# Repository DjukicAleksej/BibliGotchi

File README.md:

<div align="center">

# 🎮 BibliGotchi

<p align="center" style="font-size: 1.1em; max-width: 800px; line-height: 1.6;">
  A custom-made Tamagotchi with a heavenly touch. Made by a 17-year-old from Bosnia and Herzegovina, this project showcases my learning journey in the hardware ecosystem. I designed this using KiCad for the PCB, OnShape for the structural case, and the Arduino IDE for the firmware.
</p>

<p align="center" style="max-width: 800px; line-height: 1.6;">
  This Tamagotchi features 3 main tracking stats: <strong>Hunger</strong>, <strong>Energy</strong>, and <strong>Happiness</strong>. You can improve these parameters by physically interacting with the device using tactile buttons—each mapped to mapped behaviors like playing, feeding, or sleeping. Depending on active stats, 4 distinct screen expressions dynamically cycle: neutral, happy, sad, or sleeping. All 32x32 pixel sprites are custom-drawn, giving you the template to easily drop in your own custom artwork!
</p>

## 💡 Why Did I Build This?

<p align="center" style="max-width: 800px; line-height: 1.6;">
  I built this project to qualify for <strong>Fallout</strong>, a hardware hackathon organized by the non-profit community <strong>Hack Club</strong>. I gravitated toward building a Tamagotchi because it sits at the perfect crossroads: complex enough to challenge my design skills, yet interactive enough to stand out. In a world saturated with purely web-based apps, having a tangible, physical device makes it uniquely engaging. Through this process, I significantly deepened my understanding of firmware architecture and structural enclosure engineering.
</p>

---

<p align="center">
  <a href="Zine.pdf">📖 Read the Zine</a>
  &nbsp;&nbsp;•&nbsp;&nbsp;
  <a href="PCB-Files/Gerbers.zip">📦 Download Gerbers</a>
  &nbsp;&nbsp;•&nbsp;&nbsp;
  <a href="Case-Files/">📐 STEP Case Files</a>
  &nbsp;&nbsp;•&nbsp;&nbsp;
  <a href="BOM/BOM.csv">🧾 PCB BOM</a>
</p>

---

</div>

## 🔍 Overview
BibliGotchi is built around the **Seeed Studio XIAO ESP32-C3**, utilizing a custom PCB routed in KiCad to interface all peripherals smoothly. 

### Key Features:
* **Display**: 0.96" OLED screen for crisp UI rendering.
* **Power**: Integrated 3.7V 500mAh lithium-polymer battery.
* **Audio & Input**: Passive buzzer for alerts alongside 3 interactive navigation switches.
* **Enclosure**: Modeled inside OnShape ([View OnShape CAD Here](https://cad.onshape.com/documents/44d918d4bf107306610f1545/w/f7f086a823beff1369bb4e84/e/70df229ea8fe1c8cd39e3565)). Features filleted edge-geometry to completely eliminate sharp surfaces, precise cutouts for the USB-C port, and an internal structural sub-enclosure. The battery is safely clamped using a dual-screw retention bracket.
* **Firmware**: Written in C++ targeting the Arduino runtime environment. It implements real-time lifecycle status loops (tracking age, happiness levels, and depletion intervals) rendered via custom graphical progress bars.

---

## 📐 Case Gallery

| Top View | Top Side View |
| :---: | :---: |
|  |  |
| **Bottom View** | **Exploded View** |
|  |  |

---

## ⚡ PCB Gallery

| Top View 1 | Top View 2 |
| :---: | :---: |
|  |  |
| **Bottom View 1** | **Bottom View 2** |
|  |  |

### Schematic

---

## 🗺️ Trace Routing

| Top Routing Layer | Bottom Routing Layer |
| :---: | :---: |
|  |  |

---

### 🛠️ Bill of Materials (BOM)

| Item | Description | Value | LCSC Part | Qty | MOQ | Unit Price | Total Price | Resources |
| :--- | :--- | :--- | :--- | :---: | :---: | :---: | :---: | :--- |
| Battery | Single-cell battery | Battery_Cell | | 1 | 1 | $5.11 | $5.11 | [Datasheet](https://www.kiwi-electronics.com/image/catalog/pdf/LP503035%20500mAh%203.7V%20%28AD306053%29%2020230615%5B34%5D.pdf), [Purchase Link](https://www.aliexpress.com/item/1005006043243361.html) |
| Buzzer | Passive Buzzer | 1207-P6.5MM | C49246964 | 1 | 10 | $0.03 | $0.32 | [Datasheet](https://www.lcsc.com/datasheet/C49246964.pdf), [Purchase Link](https://www.lcsc.com/product-detail/C49246964.html) |
| Switch | Push button switch, generic, two pins | SW_Push | C2888493 | 3 | 50 | $0.01 | $0.54 | [Datasheet](https://www.lcsc.com/datasheet/C2888493.pdf), [Purchase Link](https://www.lcsc.com/product-detail/C2888493.html) |
| ESP32-C3 MCU | IoT mini development board | XIAO-ESP32-C3-SMD | | 1 | 1 | $5.67 | $5.67 | [Datasheet](https://files.seeedstudio.com/wiki/XIAO_WiFi/Resources/esp32-c3_datasheet.pdf), [Purchase Link](https://www.aliexpress.com/item/1005006979844970.html) |
| OLED Display | 0.96" Inch OLED Display | HS96L03W2C03 | C5248080 | 1 | 1 | $2.24 | $2.24 | [Datasheet](https://www.lcsc.com/datasheet/C5248080.pdf), [Purchase Link](https://www.lcsc.com/product-detail/C5248080.html) |
| PCB | Hardware Fabrication Support | - | - | 1 | 5 | - | $4.00 | - |
| PCB Shipping | Shipping for the PCB, its kinda expensive cause I live outside the EU | - | - | - | - | - | $26.00 | - |
| **Total** | | | | **8** | **68** | **$13.10** | **$43.88** | |

### ⚙️ Structural Fasteners (Build BOM)

| Item | Description | Quantity | Total Price |
| :--- | :--- | :---: | :--- |
| M3 L20 Screws | Connects the structural Bottom and Top case layers while mounting the internal PCB safely | 2 | $0.10 
| M2 Screws L8mm | Shorter structural screws allocated to tighten down the custom internal battery clamp | 2 | $0.10 
| M3 Heat Set Inserts | Threaded brass inserts allowing permanent, secure fastening profiles for outer casing | 2 | $0.10 
| M2 Heat Set Inserts | High-precision brass inserts matching structural point stabilization requirements | 2 | $0.20 
| **Total** | | **12** | **$0.60** |

---

## 🔧 Case Assembly Tutorial

### Step 1: Putting in the Battery
Seat the Battery into its enclosure in the Bottom Part, then put heat set inserts into the Battery Holder and place it onto the Battery Enclosure and screw it in.

| Align the Battery | Secure it with the Battery Holder |
| :---: | :---: |
|  |  |

### Step 2: Assembling the PCB and the Top Cover to the Bottom Part
Press-fit the M3 brass heat-set inserts straight into the designated holes inside the lower structural wall. Bring the PCB to align its mounting holes with the supports from the Bottom Part, and then Align the Top Cover so that you can screw in the top cover and bottom cover through the hole nicely,  and drive the M3 L20 screws downward to securely clamp the whole sandwich layer together.

| Put in the M3 heat set inserts | Align the PCB | Put the Top Cover Nicely aligned on the PCB |
| :--: | :---: | :---: |
|  |  |   |

---

## 💻 Firmware Setup

The runtime firmware is engineered inside the Arduino core using C++. It executes cyclic ticks tracking core stat logic while parsing interactive structural button state triggers via hardware pull-up inputs:
* **Left Button (`Feed`)**: Replenishes missing core **HUN (Hunger)** values, keeping your pet fed.
* **Middle Button (`Play`)**: Trades **-5 ENG (Energy)** to buy **+10 HAP (Happiness)** metrics.
* **Right Button (`Sleep`)**: Switches state vectors directly into the deep sleeping routine, generating a custom visual screen profile and recharging **+15 ENG (Energy)** metrics.

### Expressive Character Matrix

| Sad State (`Any Stat < 30`) | Happy State (`All Stats > 50`) |
| :---: | :---: |
|  |  |
| **Neutral State (`Standard Default`)** | **Sleep State (`Sleep Trigger Engaged`)** |
|  |  |

---

### 🚀 Compilation & Flashing Instructions

### Step 1: Install the ESP32 Board Package URL
Because ESP32 variants require platform abstraction extensions, add the official Espressif core indexes inside your environment parameters:
1. Open the **Arduino IDE**.
2. Navigate to **File** > **Preferences** (macOS: **Arduino IDE** > **Settings**).
3. Append the following address into the **Additional Boards Manager URLs** input row:
   `https://espressif.github.io/arduino-esp32/package_esp32_index.json`
   *(Note: Separate multiple indices using standard commas if you have existing entries).*
4. Click **OK** and allow indexing to finalize.

### Step 2: Fetch the Core Toolkit
1. Enter the Board Repository panel via **Tools** > **Board** > **Boards Manager**.
2. Run an evaluation sweep searching for `esp32`.
3. Locate **esp32 by Espressif Systems** and click **Install**. 
   *(Important: Verify package versions display `3.0.0` or newer to guarantee complete ESP32-C3 controller support).*

### Step 3: Instantiate local Sketch Files
Create a fresh runtime workspace profile inside the environment via **File** > **New Sketch**. Save this locally on your machine.

### Step 4: Bind Target Hardware Options
1. Go to **Tools** > **Board** > **esp32**.
2. Choose your precise module footprint: **XIAO ESP32C3**.
3. Select your system hardware serial mount path line entry under **Tools** > **Port**.

### Step 5: Resolve Peripheral Libraries
Enter the library workspace panel through **Sketch** > **Include Library** > **Manage Libraries** and search for and fetch the following dependencies:
1. **Adafruit SSD1306** (by Adafruit)
2. **Adafruit GFX Library** (by Adafruit—accept any cascading tracking dependencies if prompted)

### Step 6: Deploy Flash Assets
Link your BibliGotchi assembly to your development machine using a dependable data-rated USB-C cord. Copy the logic content found within your local `BibliGotchi_Firmware.ino` file directly over to your primary IDE sketch pane.
1. Click the **Verify** icon (the top-left checkmark layout symbol) to check for structural code errors.
2. Hit the **Upload** arrow icon situated immediately alongside it to build and flash the image over onto the controller.

### Step 7: Enjoy! 🎉
With both structural chassis parameters and software components fully synchronized, your interactive BibliGotchi buddy is officially up and running!

---

<div align="center">

Built with ❤️ by Aleksej Djukic

**BibliGotchi • Fallout 2026**

</div>

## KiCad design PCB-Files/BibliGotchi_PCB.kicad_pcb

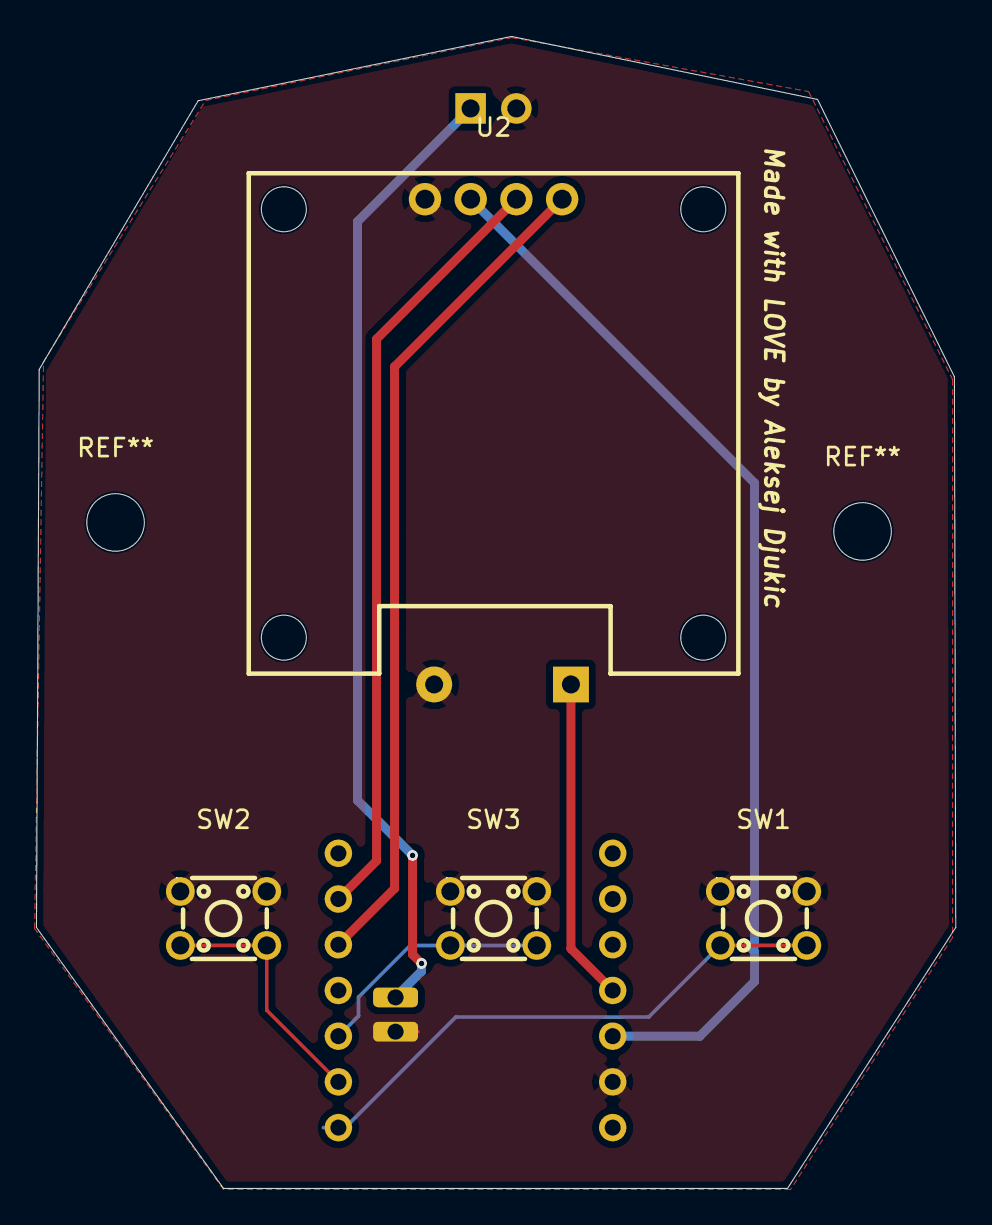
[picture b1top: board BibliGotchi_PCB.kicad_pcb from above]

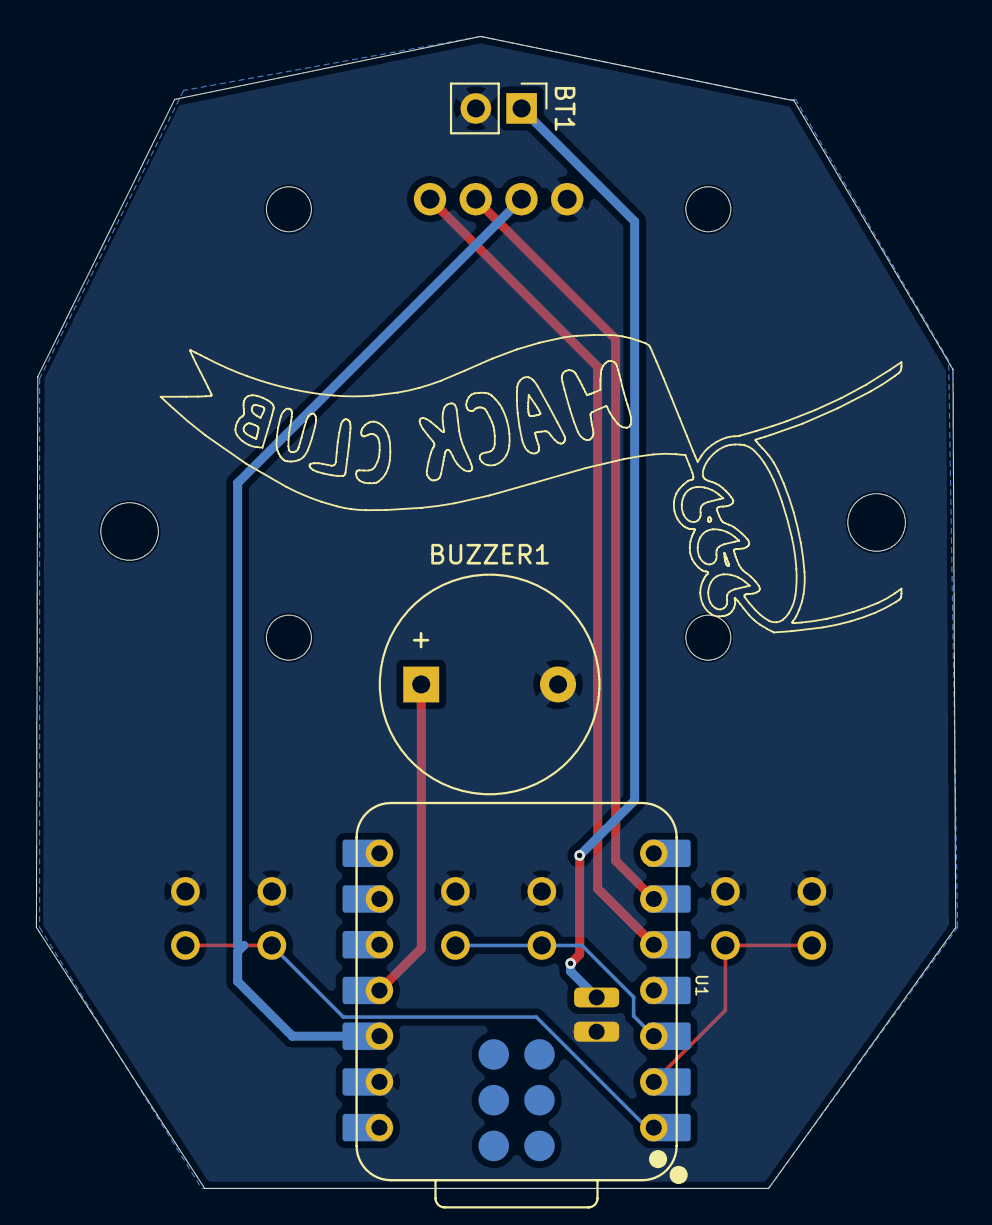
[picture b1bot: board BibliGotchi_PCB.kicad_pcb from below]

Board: 2 copper layers, 51.1 x 64.0 mm, 7 parts (3 on the bottom side), 9 nets.

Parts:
BT1: Battery_Cell; PinHeader_1x02_P2.54mm_Vertical
BUZZER1: 1207-P6.5MM; Buzzer_12x9.5RM7.6
SW1, SW2, SW3: SW_Push; SW-TH_4P-L4.5-W4.5-P3.00-LS4.8
U1: XIAO-ESP32-C3-SMD; XIAO-ESP32-C3-DIP-SMD
U2: HS96L03W2C03; OLED-TH_L27.8-W27.2-P2.54_C9900033791

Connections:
+3V3: U1.12 (3V3), U2.2 (VCC)
/+BAT: BT1.1 (+), U1.15
GND: BT1.2 (-), BUZZER1.2 (-), SW1.1, SW2.1, SW3.1, U1.13 (GND), U1.16, U2.1 (GND)
unnamed: BUZZER1.1 (+), U1.11 (GPIO10_D10_MOSI)
unnamed: SW1.2, U1.1 (GPIO2_A0_D0)
unnamed: SW2.2, U1.2 (GPIO3_A1_D1)
unnamed: SW3.2, U1.3 (GPIO4_A2_D2)
unnamed: U1.5 (GPIO6_D4_SDA), U2.4 (SDA)
unnamed: U1.6 (GPIO7_D5_SCL), U2.3 (SCL)

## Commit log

2026-06-04 Add README for BibliGotchi project
    Added project description and motivation for creating BibliGotchi.
2026-06-04 Update README with project details and image
    Added an image and improved project description.
2026-06-04 Add overview section for BibliGotchi project
    Added an overview section describing the BibliGotchi project and its features, including details about the custom PCB, OLED screen, battery, buttons, and case design.
2026-06-04 Add Bottom View and Exploded View images
    Added images for Bottom View and Exploded View to README.
2026-06-04 Enhance README with PCB design and firmware details
    Updated project description to include PCB design details and firmware information.
2026-06-04 Enhance PCB Gallery with additional views and routing
    Updated PCB Gallery section to include multiple views and added routing images.
2026-06-04 Enhance README with assembly tutorial and images
    Added detailed assembly steps and images for the case.
2026-06-04 Update image reference in assembly instructions
2026-06-05 Document firmware details in README
    Added a section about the firmware used in the project.
2026-06-05 Enhance firmware installation instructions in README
    Added detailed instructions for installing and flashing the firmware, including steps for setting up the ESP32 board in Arduino IDE.
2026-06-05 Update installation steps to unordered list format
    Changed installation steps from ordered list to unordered list.
2026-06-05 Add Bill of Materials and Build BOM sections to README
    Added a Bill of Materials (BOM) section with item details and a Build BOM section for assembly screws.
2026-06-05 Update README with image and zine link
    Added an image and a link to the zine in the README.
2026-06-05 Add footer with author and project details
    Added a footer with author information and project name.
2026-06-05 Revise README for improved presentation and details
    Updated README.md to enhance clarity and formatting.
2026-06-05 Adjust action options display alignment
    Centered action options on the display for better alignment.
2026-06-05 Add schematic section with image to README
    Added schematic image section to README.
2026-06-05 Correct ESP32 model references in README
    Updated references from ESP32-C6 to ESP32-C3 in README.
2026-06-06 Revise BOM with new components and pricing
    Updated component details and prices, added shipping costs.
2026-06-06 Update BOM.csv with new item entries
2026-06-06 Fix formatting in BOM.csv
    Removed spaces before commas and fixed formatting issues.
2026-06-06 Revise component prices and BOM structure
    Updated pricing for ESP32-C3 MCU and separated PCB and shipping costs.
2026-06-06 Modify BOM.csv to add shipping item and fix format
    Updated BOM.csv to include a new shipping item and corrected formatting.
2026-06-07 Revise assembly tutorial for battery and PCB installation
    Updated assembly steps in the tutorial to reflect new battery installation process and PCB assembly.
2026-06-07 Fix image paths in README for assembly steps
    Updated image paths in assembly instructions for clarity.
2026-06-07 Update structural fasteners list in README
    Removed M2 Screws L16mm and updated total price calculations.
